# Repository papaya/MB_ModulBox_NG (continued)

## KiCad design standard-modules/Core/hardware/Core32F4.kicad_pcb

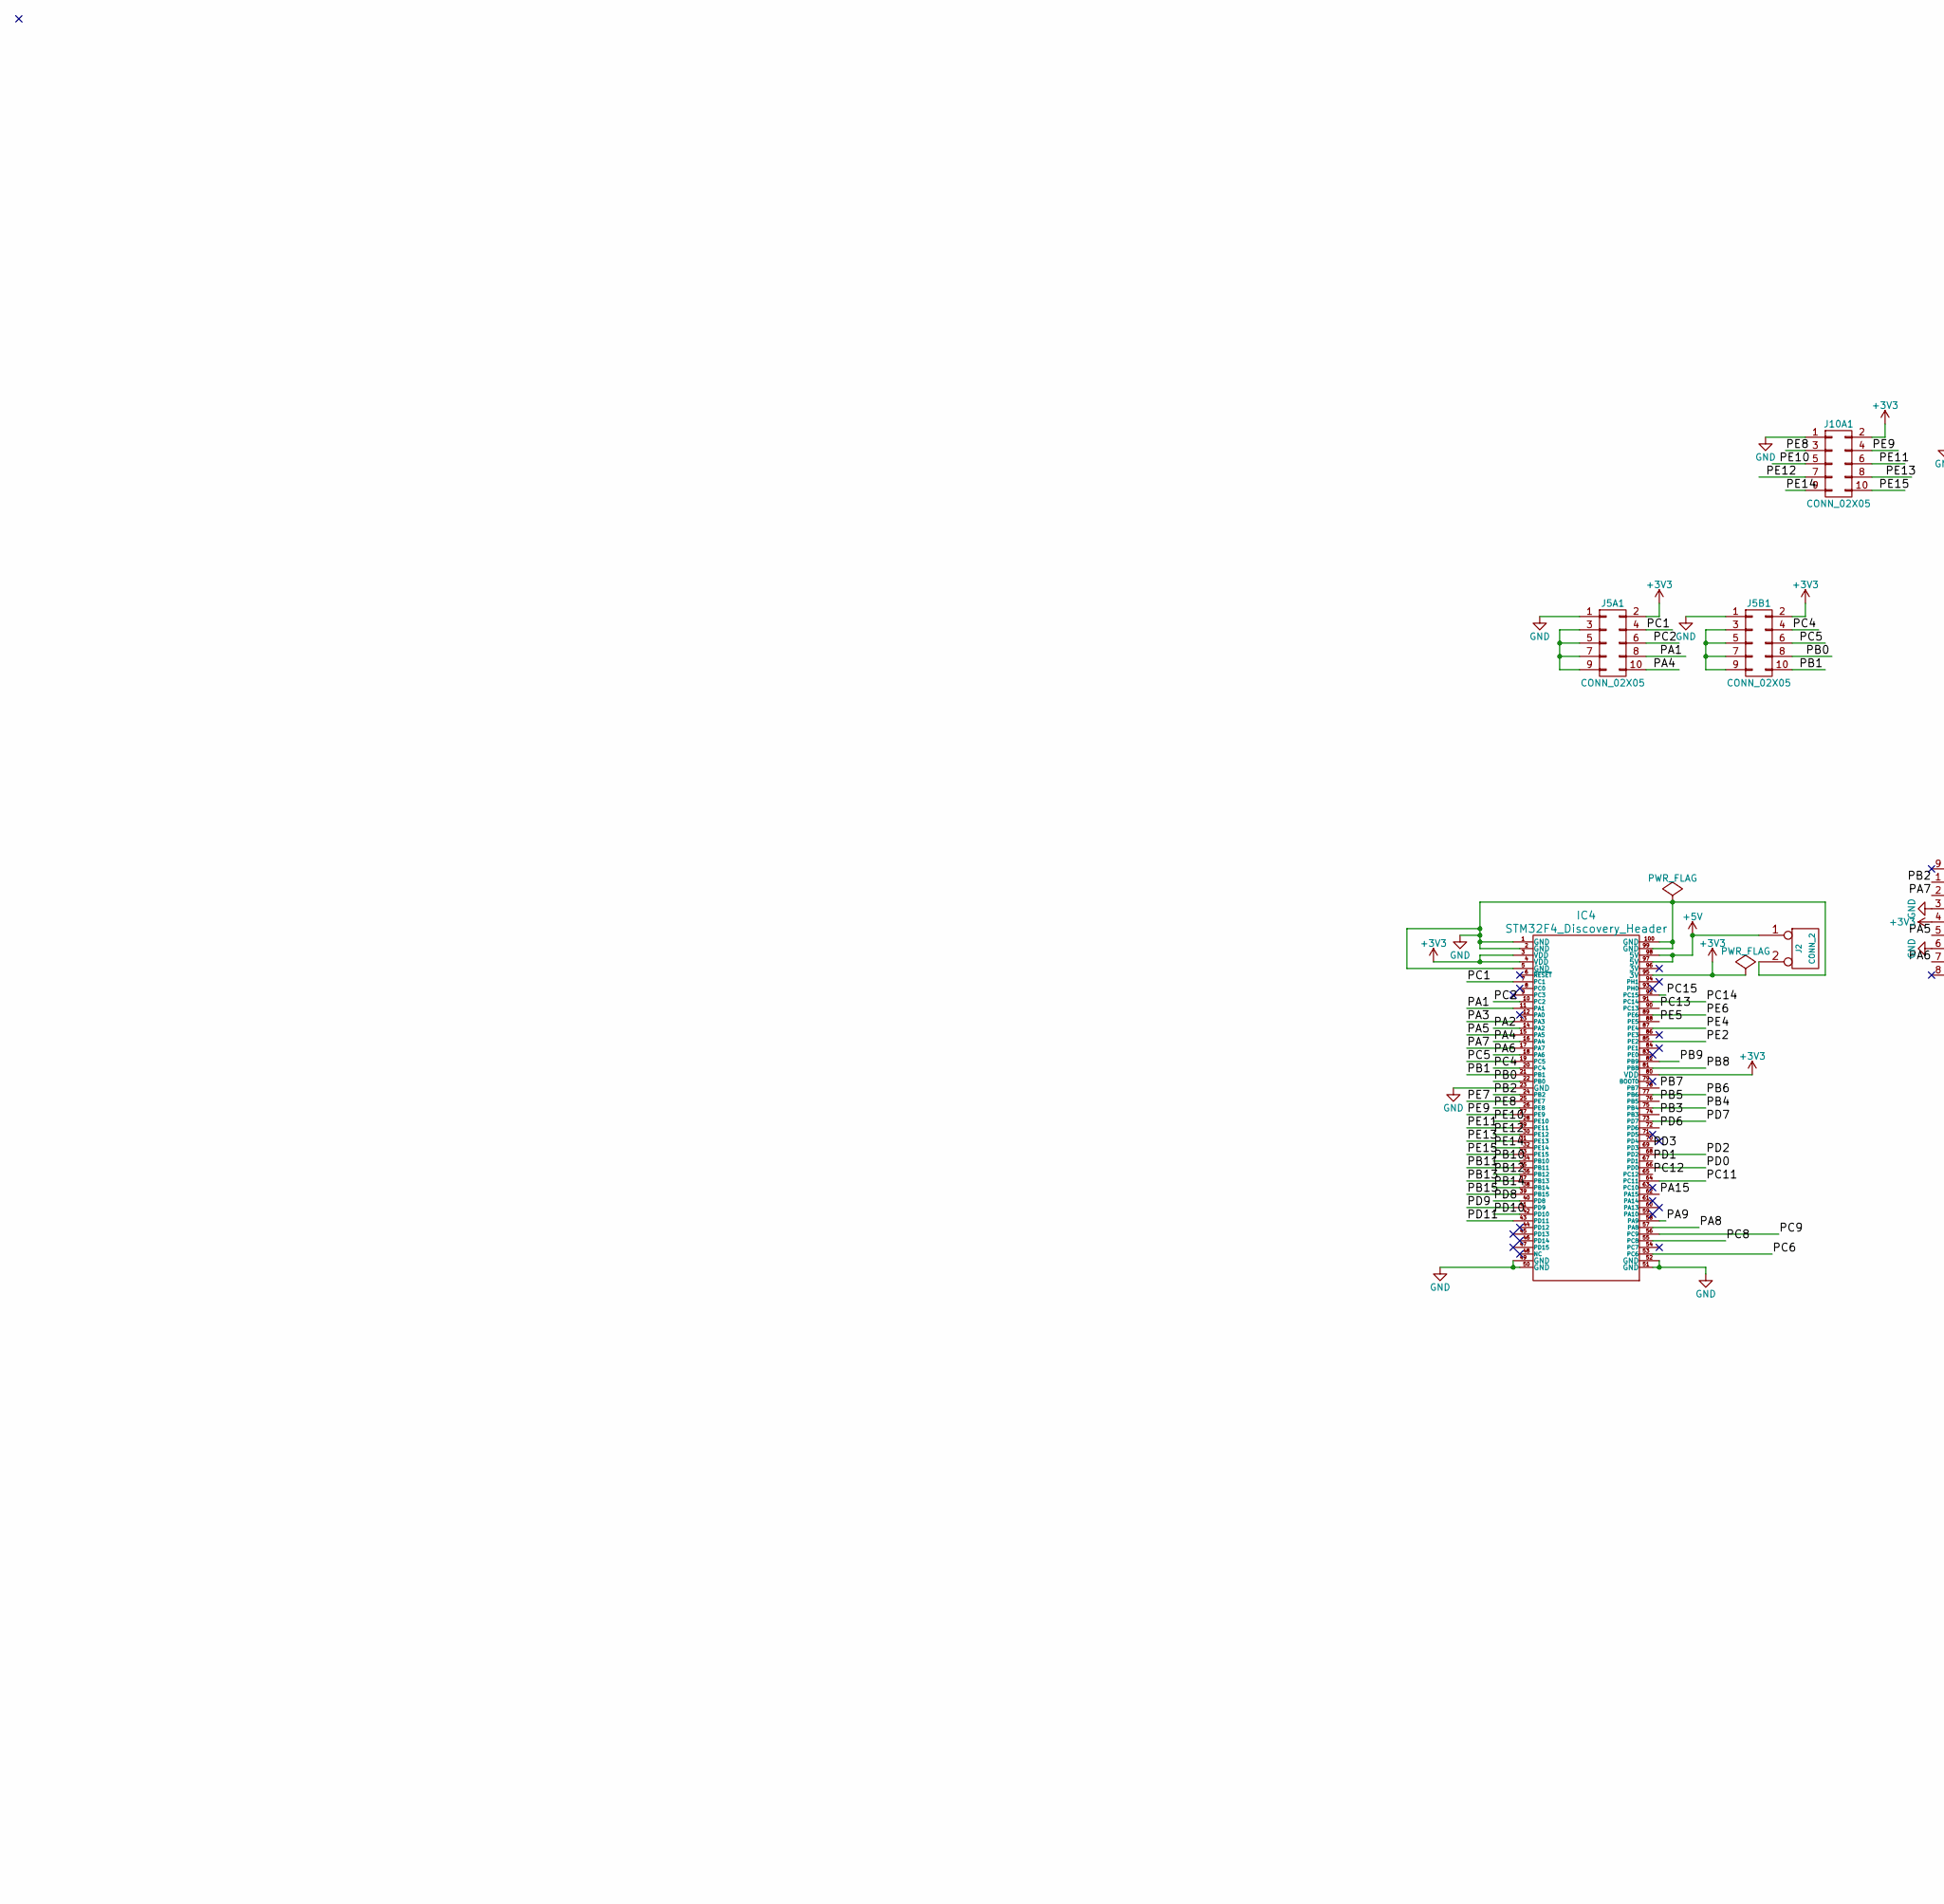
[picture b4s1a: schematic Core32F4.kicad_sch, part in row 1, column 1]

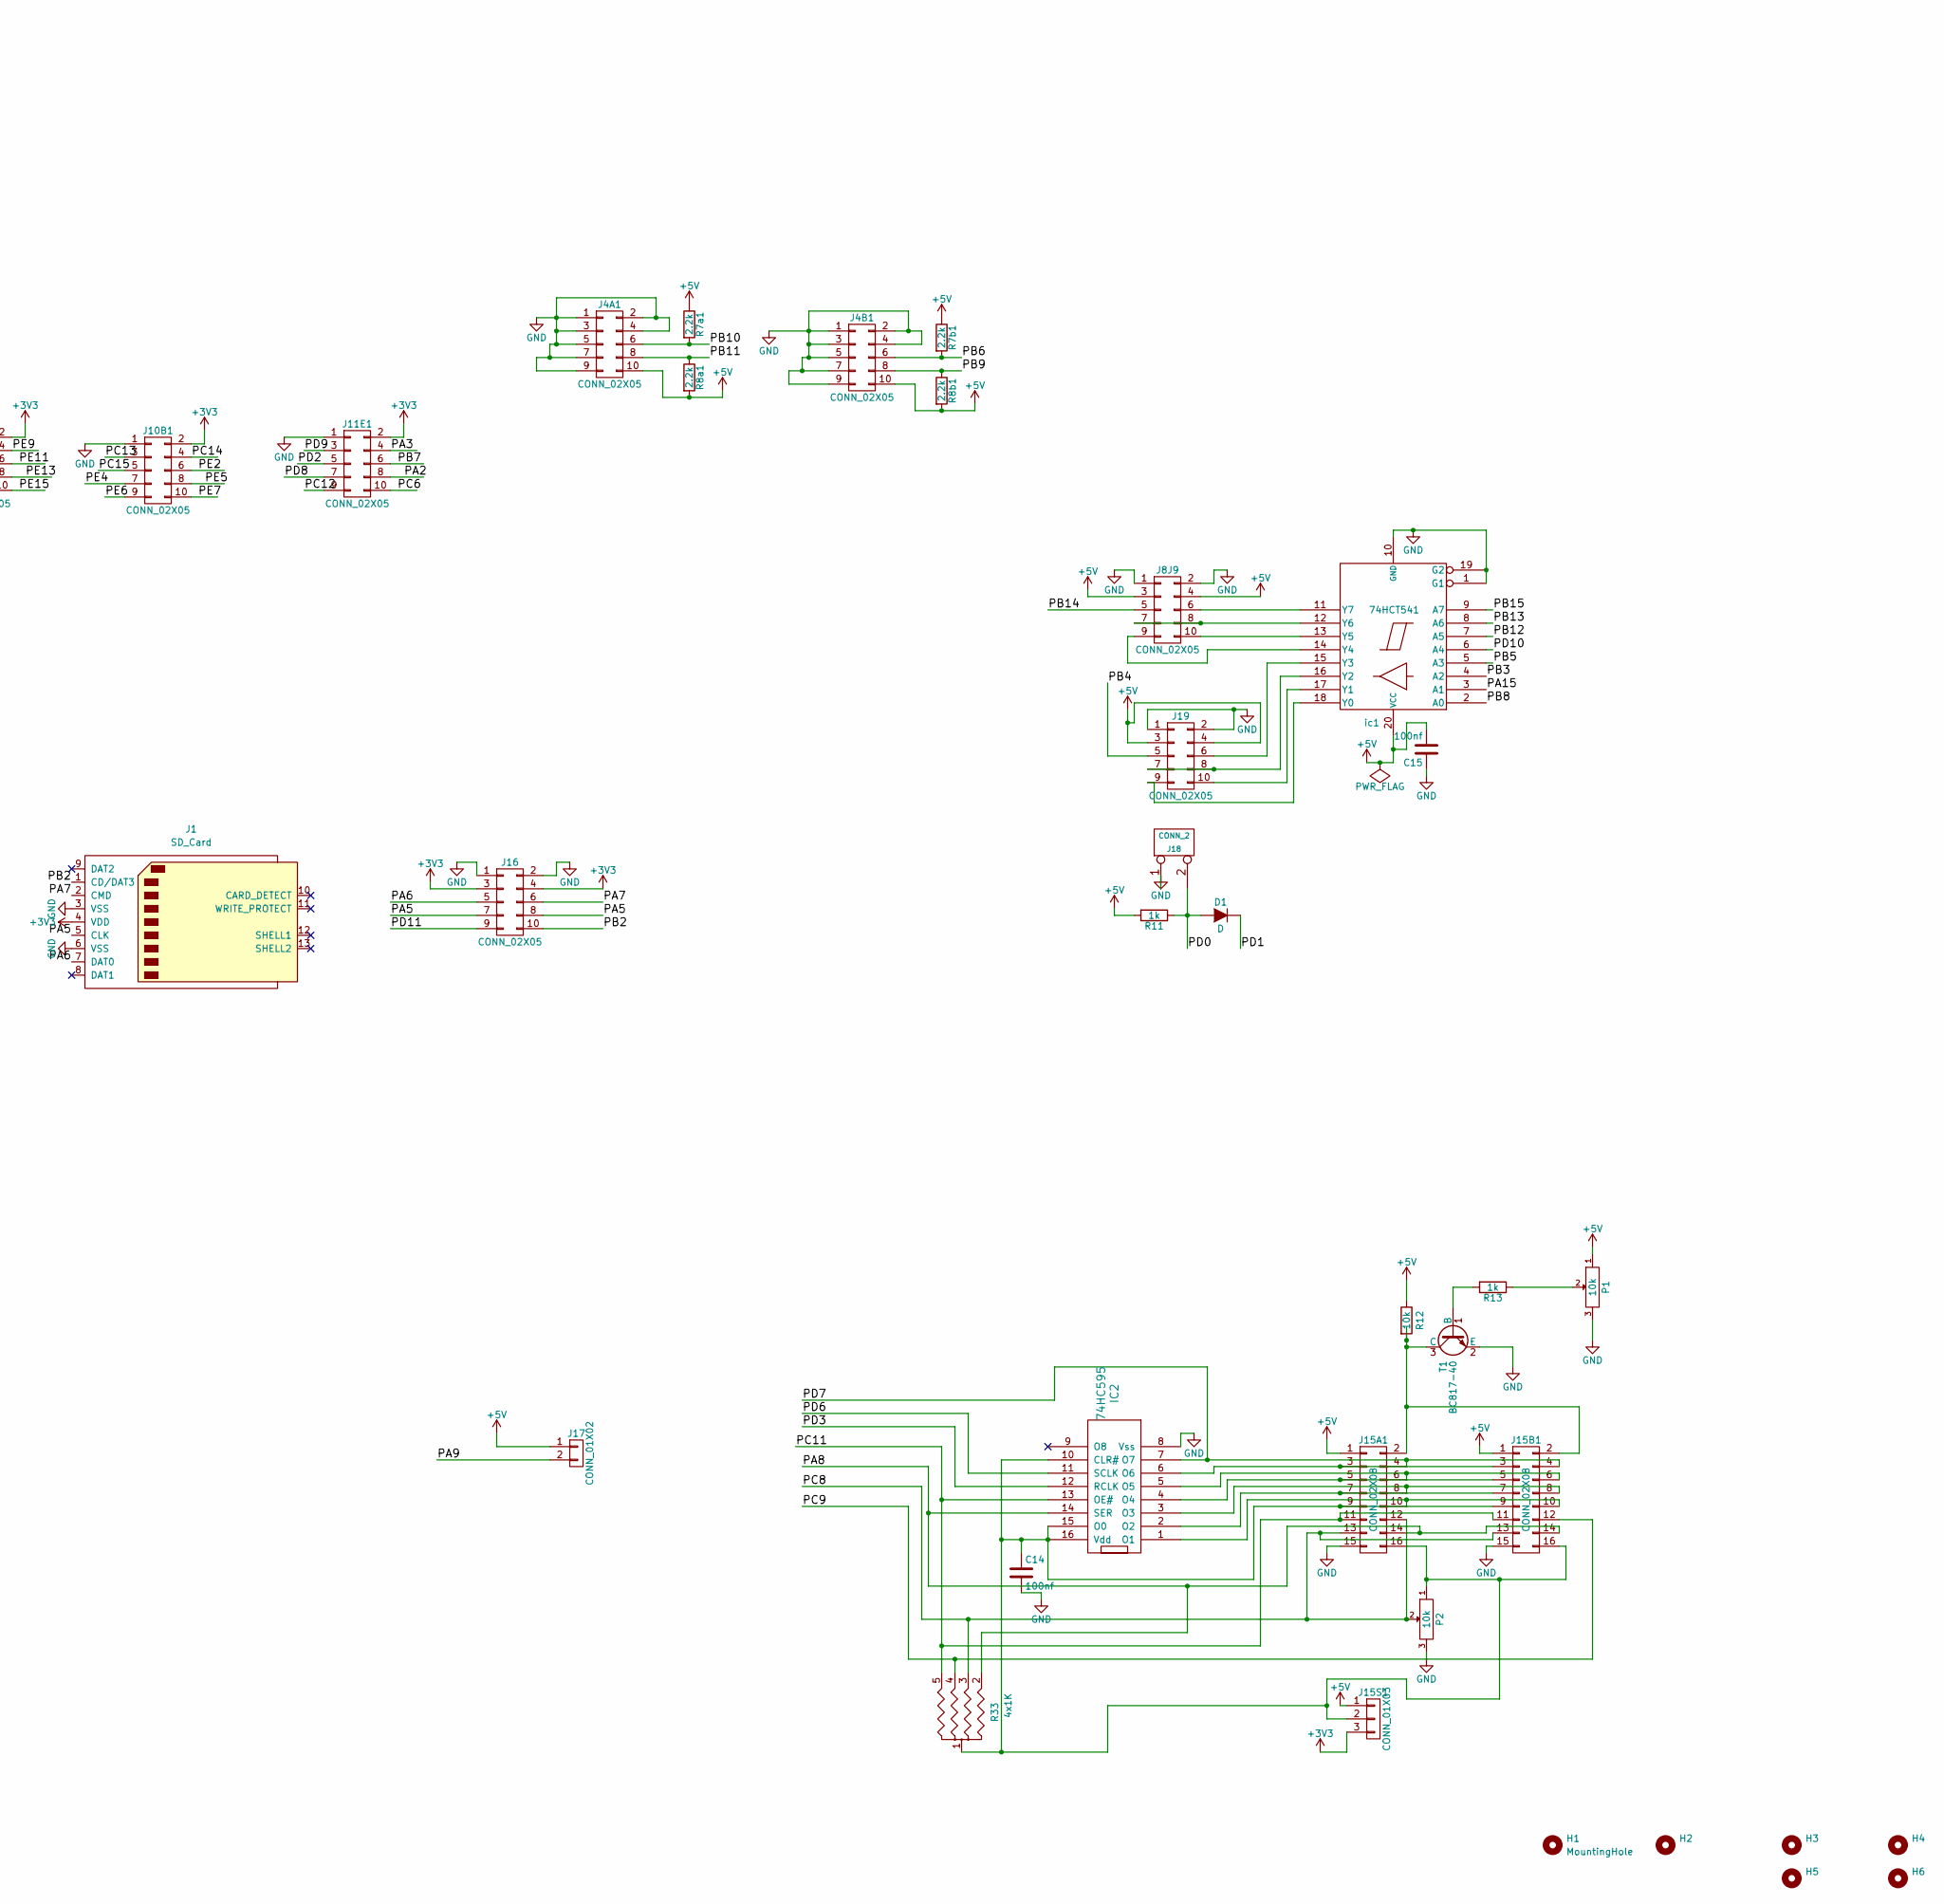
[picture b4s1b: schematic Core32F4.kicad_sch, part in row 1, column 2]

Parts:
C14, C15: 100nf; C_Disc_D3.8mm_W2.6mm_P2.50mm
D1: D; Diode_DO-35_SOD27_Horizontal_RM10
H1, H2, H3, H4, H5, H6: MountingHole; MountingHole_3.2mm_M3_ISO7380_Pad
IC2: 74HC595; DIP-16_W7.62mm_LongPads
IC4: STM32F4_Discovery_Header; stm32f4_discovery_header_ksir
J1: SD_Card; SDRSMT2MQ
J2, J18: CONN_2; PinHeader_1x02_P2.54mm_Vertical
J4A1, J4B1, J5A1, J5B1, J8J9, J10A1, J10B1, J11E1, J16, J19: CONN_02X05; IDC-Header_2x05_P2.54mm_Vertical
J15A1, J15B1: CONN_02X08; IDC-Header_2x08_P2.54mm_Vertical
J15S1: CONN_01X03; PinHeader_1x03_P2.54mm_Vertical
J17: CONN_01X02; PinHeader_1x02_P2.54mm_Vertical
P1, P2: 10k; Potentiometer_VishaySpectrol-Econtrim-Type36T
R7a1, R7b1, R8a1, R8b1: 2.2k; R_Axial_DIN0204_L3.6mm_D1.6mm_P7.62mm_Horizontal
R11, R13: 1k; R_Axial_DIN0204_L3.6mm_D1.6mm_P7.62mm_Horizontal
R12: 10k; R_Axial_DIN0204_L3.6mm_D1.6mm_P7.62mm_Horizontal
R33: 4x1K; R_Array_SIP5
T1: BC817-40; bc337
ic1: 74HCT541; DIP-20_W7.62mm_LongPads

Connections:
+3V3: IC4.3 (VDD), IC4.4 (VDD), IC4.80 (VDD), IC4.95 (3V), J1.4 (VDD), J5A1.2, J5B1.2, J10A1.2, J10B1.2, J11E1.2, J15S1.3, J16.3, J16.4
+5V: C15.2, IC4.97 (5V), IC4.98 (5V), J2.1, J4A1.10, J4B1.10, J8J9.3, J8J9.4, J15A1.1, J15B1.1, J15S1.1, J17.1, J19.3, J19.4, P1.1, R7a1.1, R7b1.1, R8a1.2, R8b1.2, R11.2, R12.1, ic1.20 (VCC)
/PA1: IC4.11 (PA1), J5A1.8
/PA2: IC4.14 (PA2), J11E1.8
/PA3: IC4.13 (PA3), J11E1.4
/PA4: IC4.16 (PA4), J5A1.10
/PA5: IC4.15 (PA5), J1.5 (CLK), J16.7, J16.8
/PA6: IC4.18 (PA6), J1.7 (DAT0), J16.5
/PA7: IC4.17 (PA7), J1.2 (CMD), J16.6
/PA8: IC2.14 (SER), IC4.57 (PA8), J15A1.14, J15B1.14, R33.2
/PA9: IC4.58 (PA9), J17.2
/PA15: IC4.62 (PA15), ic1.3 (A1)
/PB0: IC4.22 (PB0), J5B1.8
/PB1: IC4.21 (PB1), J5B1.10
/PB2: IC4.24 (PB2), J1.1 (CD/DAT3), J16.10
/PB3: IC4.74 (PB3), ic1.4 (A2)
/PB4: IC4.75 (PB4), J19.5
/PB5: IC4.76 (PB5), ic1.5 (A3)
/PB6: IC4.77 (PB6), J4B1.6, R7b1.2
/PB7: IC4.78 (PB7), J11E1.6
/PB8: IC4.81 (PB8), ic1.2 (A0)
/PB9: IC4.82 (PB9), J4B1.8, R8b1.1
/PB10: IC4.34 (PB10), J4A1.6, R7a1.2
/PB11: IC4.35 (PB11), J4A1.8, R8a1.1
/PB12: IC4.36 (PB12), ic1.7 (A5)
/PB13: IC4.37 (PB13), ic1.8 (A6)
/PB14: IC4.38 (PB14), J8J9.5
/PB15: IC4.39 (PB15), ic1.9 (A7)
/PC1: IC4.7 (PC1), J5A1.4
/PC2: IC4.10 (PC2), J5A1.6
/PC4: IC4.20 (PC4), J5B1.4
/PC5: IC4.19 (PC5), J5B1.6
/PC6: IC4.53 (PC6), J11E1.10
/PC8: IC4.55 (PC8), J15A1.12, J15A1.13, J15B1.13, P2.2, R33.3
/PC11: IC2.13 (OE#), IC4.64 (PC11), J15A1.11, J15B1.11, R33.5
/PC12: IC4.65 (PC12), J11E1.9
/PC13: IC4.90 (PC13), J10B1.3
/PC14: IC4.91 (PC14), J10B1.4
/PC15: IC4.92 (PC15), J10B1.5
/PD0: D1.2 (A), IC4.66 (PD0), J18.2 (PM), R11.1
/PD1: D1.1 (K), IC4.67 (PD1)
/PD2: IC4.68 (PD2), J11E1.5
/PD3: IC2.12 (RCLK), IC4.69 (PD3)
/PD6: IC2.11 (SCLK), IC4.72 (PD6)
/PD7: IC2.7 (O7), IC4.73 (PD7), J15A1.4, J15B1.4
/PD8: IC4.40 (PD8), J11E1.7
/PD9: IC4.41 (PD9), J11E1.3
/PD10: IC4.42 (PD10), ic1.6 (A4)
/PD11: IC4.43 (PD11), J16.9
/PE2: IC4.85 (PE2), J10B1.6
/PE4: IC4.87 (PE4), J10B1.7
/PE5: IC4.88 (PE5), J10B1.8
/PE6: IC4.89 (PE6), J10B1.9
/PE7: IC4.25 (PE7), J10B1.10
/PE8: IC4.26 (PE8), J10A1.3
/PE9: IC4.27 (PE9), J10A1.4
/PE10: IC4.28 (PE10), J10A1.5
/PE11: IC4.29 (PE11), J10A1.6
/PE12: IC4.30 (PE12), J10A1.7
/PE13: IC4.31 (PE13), J10A1.8
/PE14: IC4.32 (PE14), J10A1.9
/PE15: IC4.33 (PE15), J10A1.10
unnamed: C14.1, IC2.10 (CLR#), IC2.15 (O0), IC2.16 (Vdd), J15A1.9, J15A1.16, J15B1.9, J15B1.16, J15S1.2, P2.1, R33.1
unnamed: IC2.1 (O1), J15A1.10, J15B1.10
unnamed: IC2.2 (O2), J15A1.7, J15B1.7
unnamed: IC2.3 (O3), J15A1.8, J15B1.8
unnamed: IC2.4 (O4), J15A1.5, J15B1.5
unnamed: IC2.5 (O5), J15A1.6, J15B1.6
unnamed: IC2.6 (O6), J15A1.3, J15B1.3
unnamed: J5A1.3, J5A1.5, J5A1.7, J5A1.9
unnamed: J5B1.3, J5B1.5, J5B1.7, J5B1.9
unnamed: J8J9.6, ic1.11 (Y7)
unnamed: J8J9.7, J8J9.8, ic1.12 (Y6)
unnamed: J8J9.9, ic1.14 (Y4)
unnamed: J8J9.10, ic1.13 (Y5)
unnamed: J15A1.2, J15B1.2, R12.2, T1.3 (C)
unnamed: J19.6, ic1.15 (Y3)
unnamed: J19.7, J19.8, ic1.16 (Y2)
unnamed: J19.9, ic1.18 (Y0)
unnamed: J19.10, ic1.17 (Y1)
unnamed: P1.2, R13.1
unnamed: R13.2, T1.1 (B)

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
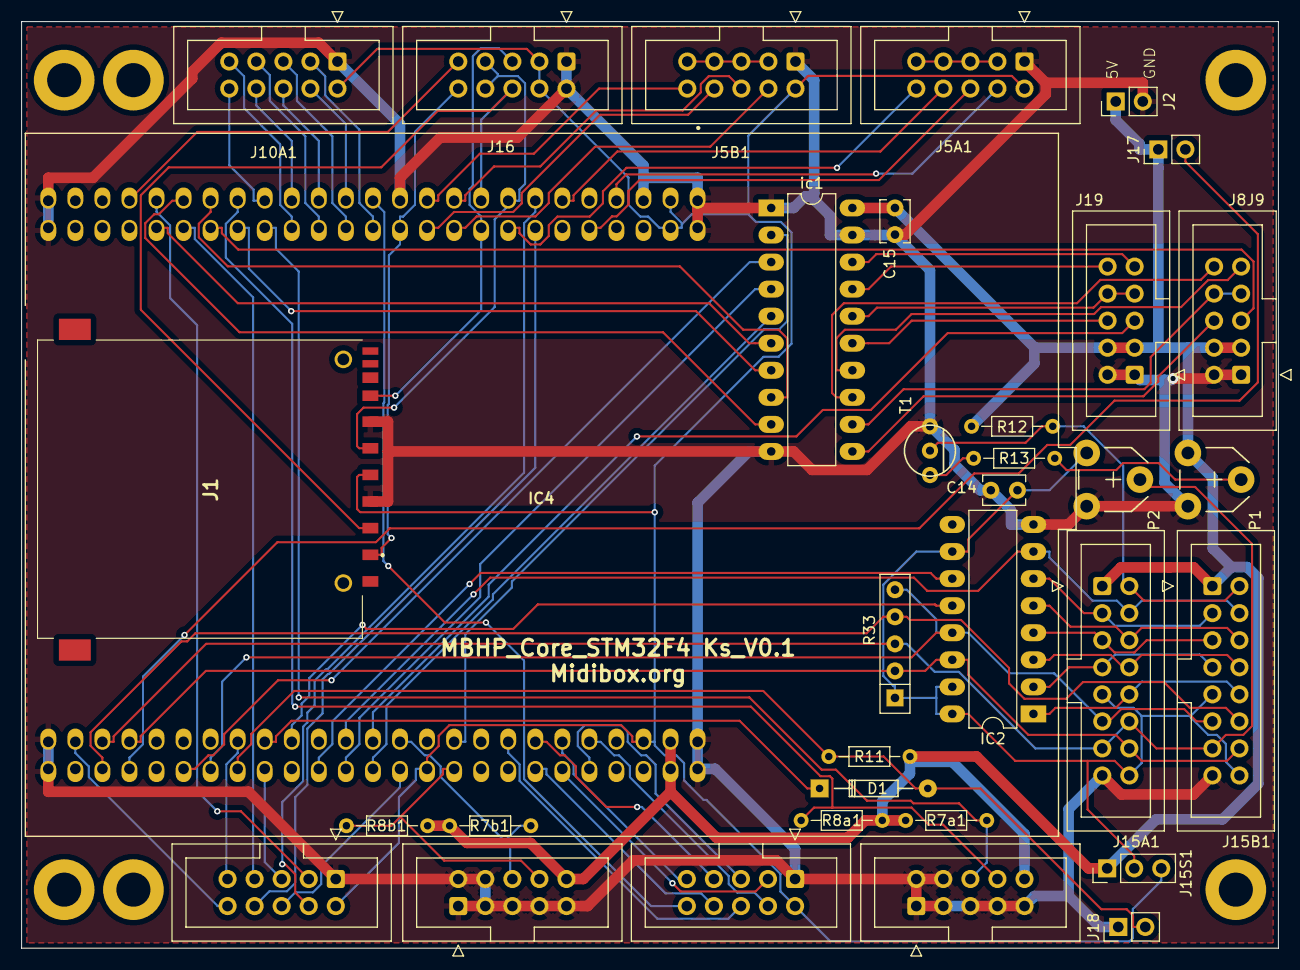
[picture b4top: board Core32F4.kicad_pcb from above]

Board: 2 copper layers, 118.0 x 87.0 mm, 40 parts (0 on the bottom side), 84 nets.

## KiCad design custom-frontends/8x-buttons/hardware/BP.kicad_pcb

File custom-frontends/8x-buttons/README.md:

# 8x-buttons — Module custom 8 boutons poussoirs (DIN + DOUT)

## Description

Module boutons poussoirs (8 canaux) pour l'envoi d'événements MIDI numériques (Note On/Off, CC, etc.). La carte se branche sur le **bus DIN** (entrées digitales) du contrôleur MIDIbox NG et fournit en plus **8 sorties DOUT** pour piloter des LEDs.

## Spécifications techniques

- 8 boutons poussoirs mécaniques **à LED incorporée** (empreinte `switch_led_mec`)
- 8 LED supplémentaires (empreinte `LED Switch mec`), câblées en sortie
- **2 connecteurs IDC 2x05 P2.54mm** : `J1` = 8 entrées DIN, `J2` = 8 sorties DOUT
- **Aucune résistance de pull-up sur la carte** : le pull-up 10 kΩ est porté par le module **DIN** (74HC165), conformément à la référence MIDIbox
- Aucun registre à décalage sur la carte : les entrées et sorties sont balayées par les registres du module DIN / DOUT

## Composants principaux

| Type | Dénomination | Qté |
|------|-------------|-----|
| Bouton poussoir mécanique à LED | `switch_led_mec` | 8 |
| LED | `LED Switch mec` | 8 |
| Connecteur | IDC Header 2x05 P2.54mm Vertical (`J1`, `J2`) | 2 |
| Vis de fixation | MountingHole 3.2mm M3 | 4 |

> Les versions antérieures de cette page mentionnaient un **connecteur D-Sub 24 broches** et **8 pull-ups 10 kΩ** sur la carte : **ces deux éléments sont absents du schéma KiCad**. Le raccordement se fait par IDC 2x05.

## Brochage / Mapping MIDIbox NG

### `J1` — 8 entrées DIN (vers le module DIN 74HC165, chainage `J8`/`J9` du Core)

| Broche | Signal | Description |
|--------|--------|-------------|
| 1 | GND | Masse commune (contact du bouton) |
| 2 | — | Non connectée |
| 3 | `J1-D7` | Bouton **SW8** |
| 4 | `J1-D6` | Bouton **SW7** |
| 5 | `J1-D5` | Bouton **SW6** |
| 6 | `J1-D4` | Bouton **SW5** |
| 7 | `J1-D3` | Bouton **SW4** |
| 8 | `J1-D2` | Bouton **SW3** |
| 9 | `J1-D1` | Bouton **SW2** |
| 10 | `J1-D0` | Bouton **SW1** |

> Chaque bouton est un contact **entre sa broche `J1-Dx` et GND** (broche 1). Le niveau haut est assuré par le pull-up 10 kΩ du module DIN.

### `J2` — 8 sorties DOUT (vers le module DOUT 74HC595, chainage `J8`/`J9` du Core)

| Broche | Signal | Description |
|--------|--------|-------------|
| 1 | GND | Masse commune (cathode des LED) |
| 2 | — | Non connectée |
| 3 | `D8-A` | LED **D8** (anode) |
| 4 | `D7-A` | LED **D7** (anode) |
| 5 | `D6-A` | LED **D6** (anode) |
| 6 | `D5-A` | LED **D5** (anode) |
| 7 | `D4-A` | LED **D4** (anode) |
| 8 | `D3-A` | LED **D3** (anode) |
| 9 | `D2-A` | LED **D2** (anode) |
| 10 | `D1-A` | LED **D1** (anode) |

> L'anode de chaque LED est tirée vers la sortie DOUT correspondante ; la cathode est sur GND. La résistance de limitation (**220 Ω**) est portée par le module **DOUT** (74HC595), pas par cette carte.

## Notes de montage et astuces DIY

- Vérifier la configuration des entrées (active haut / active bas) avant câblage
- Pour un fonctionnement « high-active », il faut inverser le câblage du pull-up côté module DIN (procédure décrite sur [ucapps.de/mbhp_din](https://www.ucapps.de/mbhp_din.html))
- La LED de chaque bouton est câblée indépendamment sur `J2` : une LED du bouton peut être allumée indépendamment de l'état du bouton

## Documentation de fabrication

- `hardware/` : sources KiCad (`BP.*`)
- `hardware/3D/` : modèle 3D du boîtier (`BP V3.wrl`)
- `production/` : Gerbers, BOM (`bom.csv`), netlist, archives de fabrication
## Assets de visualisation

| Type | Fichier | Description |
|------|---------|-------------|
| Top view | `3d-top.png` | Vue de dessus du PCB |
| Screenshot 1 | `Screenshot%202023-05-19%20163416.png` | Capture d'écran du design |
| Screenshot 2 | `Screenshot%202023-05-19%20202624.png` | Capture d'écran du design |
---

## Conception & Compatibilité

Carte d'interface **originale MB MODULBOX NG** (conception Ksir), compatible avec les bus et modules du système MIDIbox NG. Ce n'est **pas** un module officiel MIDIbox.

> **Origine et usage :** conception originale MB MODULBOX NG, prévue pour le DIY/personnel. Aucune licence formelle n'est publiée dans le dépôt ; voir le README racine. **Aucune garantie ni engagement** n'est fourni sur la justesse du câblage ou du routage.

> ⚠️ **Avertissement :** documentation de passion, **non professionnelle**. Fournie **sans garantie ni engagement**, **sans support technique**. Des **erreurs sont possibles** (schémas, valeurs, câblage). À vos risques et périls : vérifiez tout avant de fabriquer et de mettre sous tension.

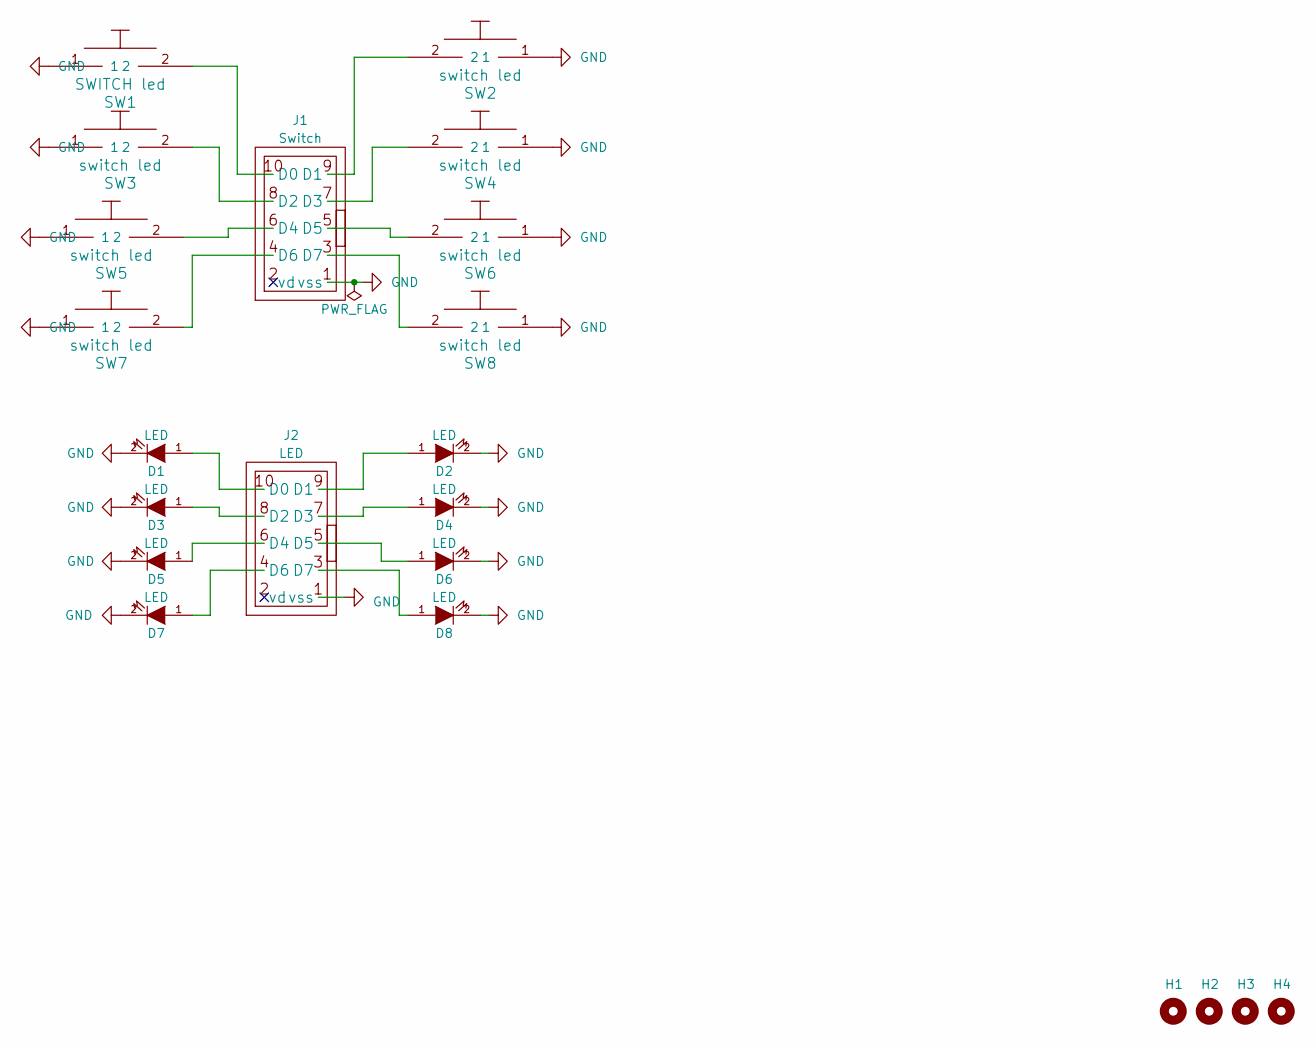
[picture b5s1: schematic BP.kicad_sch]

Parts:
D1, D2, D3, D4, D5, D6, D7, D8: LED; LED Switch mec
H1, H2, H3, H4: MountingHole; MountingHole_3.2mm_M3
J1, J2: IDC-Header_2x05_P2.54mm_Vertical
SW1: SWITCH led; switch_led_mec
SW2, SW3, SW4, SW5, SW6, SW7, SW8: switch led; switch_led_mec

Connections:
GND: D1.2 (K), D2.2 (K), D3.2 (K), D4.2 (K), D5.2 (K), D6.2 (K), D7.2 (K), D8.2 (K), J1.1 (vss), J2.1 (vss), SW1.1, SW2.1, SW3.1, SW4.1, SW5.1, SW6.1, SW7.1, SW8.1
unnamed: D1.1 (A), J2.10 (D0)
unnamed: D2.1 (A), J2.9 (D1)
unnamed: D3.1 (A), J2.8 (D2)
unnamed: D4.1 (A), J2.7 (D3)
unnamed: D5.1 (A), J2.6 (D4)
unnamed: D6.1 (A), J2.5 (D5)
unnamed: D7.1 (A), J2.4 (D6)
unnamed: D8.1 (A), J2.3 (D7)
unnamed: J1.10 (D0), SW1.2
unnamed: J1.9 (D1), SW2.2
unnamed: J1.8 (D2), SW3.2
unnamed: J1.7 (D3), SW4.2
unnamed: J1.6 (D4), SW5.2
unnamed: J1.5 (D5), SW6.2
unnamed: J1.4 (D6), SW7.2
unnamed: J1.3 (D7), SW8.2

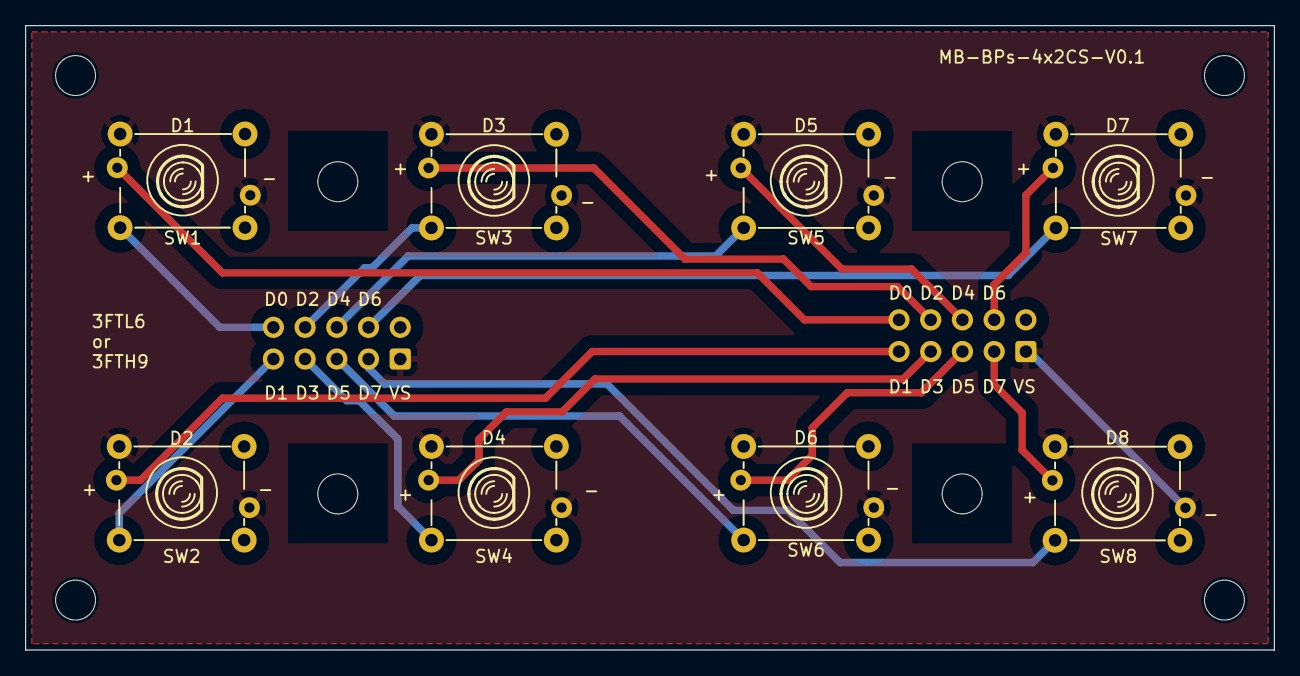
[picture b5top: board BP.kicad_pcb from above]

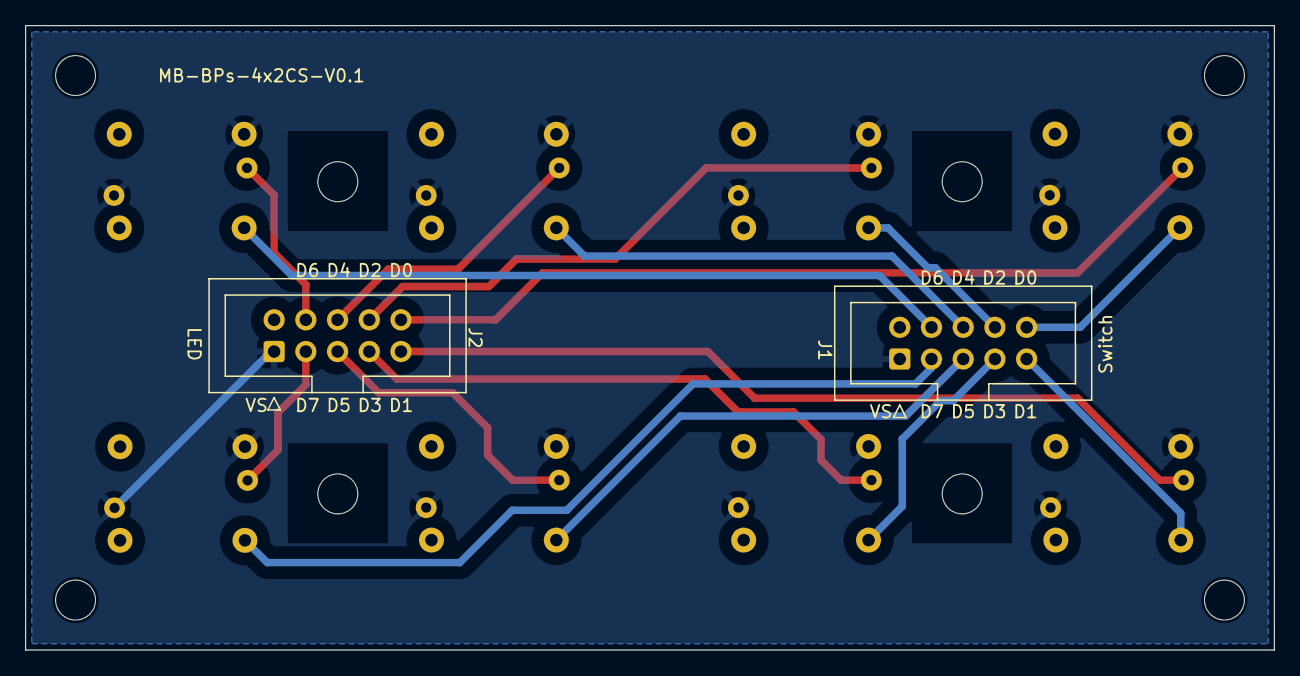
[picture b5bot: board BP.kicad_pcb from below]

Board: 2 copper layers, 100.0 x 50.0 mm, 26 parts (2 on the bottom side), 17 nets.

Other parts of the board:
H1#2, H2#2, H3#2, H4#2: MountingHole; MountingHole_3.2mm_M3

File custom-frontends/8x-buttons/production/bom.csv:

Designator,Footprint,Quantity,Value,LCSC Part #
"D1, D2, D3, D4, D5, D6, D7, D8",LED Switch mec,8,LED,
ENC1,EC12E24204A8,1,MENU,
"H1_3, H1_2, H1, H2_3, H2_2, H2, H3_3, H3_2, H3, H4_3, H4_2, H4",MountingHole_3.2mm_M3,12,MountingHole,
"J1, J2_2, J2",IDC-Header_2x05_P2.54mm_Vertical,3,IDC-Header_2x05_P2.54mm_Vertical,
"SW1, SW2, SW3, SW4, SW5, SW6, SW7, SW8",switch_led_mec,8,SWITCH led,
SWc1,124110828,1,shift,
SWc2,124110828,1,soft4,
SWc3,124110828,1,soft 3,
SWc4,124110828,1,soft 2,
SWc5,124110828,1,soft 1,
SWc6,124110828,1,MENU,

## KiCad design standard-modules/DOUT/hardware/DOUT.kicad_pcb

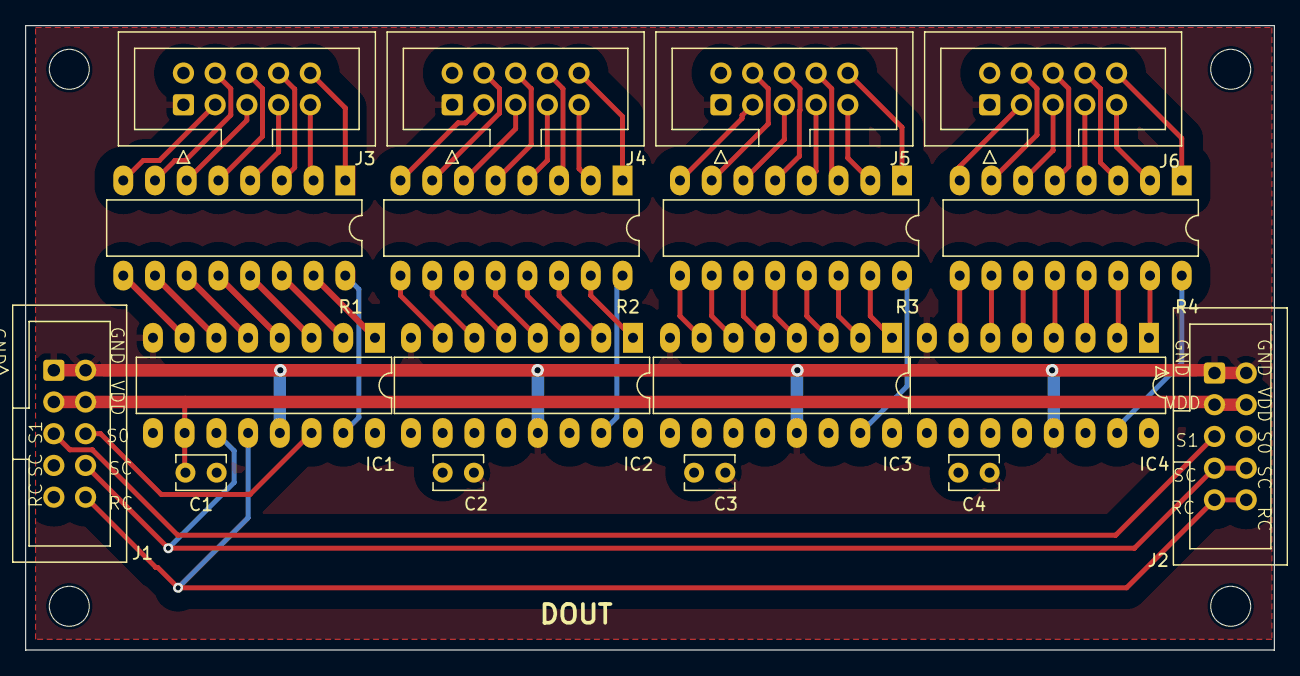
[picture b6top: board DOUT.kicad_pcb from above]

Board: 2 copper layers, 100.0 x 50.0 mm, 22 parts (0 on the bottom side), 74 nets.

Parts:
C1, C2, C3, C4: 100NF; C_Disc_D3.8mm_W2.6mm_P2.50mm
H1, H2, H3, H4: MountingHole; MountingHole_3.2mm_M3
IC1, IC2, IC3, IC4: SN74HC595N; DIP-16_74h595
J1, J2: sin_in; IDC-Header_2x05_P2.54mm_Vertical_ksr_TO_J8_J9
J3, J4, J5, J6: sin_in; IDC-Header_2x05_P2.54mm_Vertical
R1: 220 ohm; DIP-16_R220_network
R2, R3, R4: 220 ohm; DIP-16_W7.62mm_LongPads

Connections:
+5V: C1.2, C2.2, C3.2, C4.2, IC1.10 (~SRCLR), IC1.16 (VCC), IC2.10 (~SRCLR), IC2.16 (VCC), IC3.10 (~SRCLR), IC3.16 (VCC), IC4.10 (~SRCLR), IC4.16 (VCC), J1.3, J1.4, J2.3, J2.4
/DOUT_RC: IC1.12 (RCLK), IC2.12 (RCLK), IC3.12 (RCLK), IC4.12 (RCLK), J1.10, J2.9, J2.10
/DOUT_SC: IC1.11 (SRCLK), IC2.11 (SRCLK), IC3.11 (SRCLK), IC4.11 (SRCLK), J1.8, J2.7, J2.8
/S0: IC1.14 (SER), J1.6
GND: C1.1, C2.1, C3.1, C4.1, IC1.8 (GND), IC1.13 (~OE), IC2.8 (GND), IC2.13 (~OE), IC3.8 (GND), IC3.13 (~OE), IC4.8 (GND), IC4.13 (~OE), J1.1, J1.2, J2.1, J2.2, J3.1, J4.1, J5.1, J6.1
unnamed: IC1.15 (QA), R1.16 (R1.2)
unnamed: IC1.1 (QB), R1.15 (R2.2)
unnamed: IC1.2 (QC), R1.14 (R3.2)
unnamed: IC1.3 (QD), R1.13 (R4.2)
unnamed: IC1.4 (QE), R1.12 (R5.2)
unnamed: IC1.5 (QF), R1.11 (R6.2)
unnamed: IC1.6 (QG), R1.10 (R7.2)
unnamed: IC1.7 (QH_1), R1.9 (R8.2)
unnamed: IC1.9 (QH_2), IC2.14 (SER)
unnamed: IC2.15 (QA), R2.16 (R1.2)
unnamed: IC2.1 (QB), R2.15 (R2.2)
unnamed: IC2.2 (QC), R2.14 (R3.2)
unnamed: IC2.3 (QD), R2.13 (R4.2)
unnamed: IC2.4 (QE), R2.12 (R5.2)
unnamed: IC2.5 (QF), R2.11 (R6.2)
unnamed: IC2.6 (QG), R2.10 (R7.2)
unnamed: IC2.7 (QH_1), R2.9 (R8.2)
unnamed: IC2.9 (QH_2), IC3.14 (SER)
unnamed: IC3.15 (QA), R3.16 (R1.2)
unnamed: IC3.1 (QB), R3.15 (R2.2)
unnamed: IC3.2 (QC), R3.14 (R3.2)
unnamed: IC3.3 (QD), R3.13 (R4.2)
unnamed: IC3.4 (QE), R3.12 (R5.2)
unnamed: IC3.5 (QF), R3.11 (R6.2)
unnamed: IC3.6 (QG), R3.10 (R7.2)
unnamed: IC3.7 (QH_1), R3.9 (R8.2)
unnamed: IC3.9 (QH_2), IC4.14 (SER)
unnamed: IC4.15 (QA), R4.16 (R1.2)
unnamed: IC4.1 (QB), R4.15 (R2.2)
unnamed: IC4.2 (QC), R4.14 (R3.2)
unnamed: IC4.3 (QD), R4.13 (R4.2)
unnamed: IC4.4 (QE), R4.12 (R5.2)
unnamed: IC4.5 (QF), R4.11 (R6.2)
unnamed: IC4.6 (QG), R4.10 (R7.2)
unnamed: IC4.7 (QH_1), R4.9 (R8.2)
unnamed: IC4.9 (QH_2), J2.6
unnamed: J1.5, J2.5
unnamed: J3.10, R1.1 (R1.1)
unnamed: J3.9, R1.2 (R2.1)
unnamed: J3.8, R1.3 (R3.1)
unnamed: J3.7, R1.4 (R4.1)
unnamed: J3.6, R1.5 (R5.1)
unnamed: J3.5, R1.6 (R6.1)
unnamed: J3.4, R1.7 (R7.1)
unnamed: J3.3, R1.8 (R8.1)
unnamed: J4.10, R2.1 (R1.1)
unnamed: J4.9, R2.2 (R2.1)
unnamed: J4.8, R2.3 (R3.1)
unnamed: J4.7, R2.4 (R4.1)
unnamed: J4.6, R2.5 (R5.1)
unnamed: J4.5, R2.6 (R6.1)
unnamed: J4.4, R2.7 (R7.1)
unnamed: J4.3, R2.8 (R8.1)
unnamed: J5.10, R3.1 (R1.1)
unnamed: J5.9, R3.2 (R2.1)
unnamed: J5.8, R3.3 (R3.1)
unnamed: J5.7, R3.4 (R4.1)
unnamed: J5.6, R3.5 (R5.1)
unnamed: J5.5, R3.6 (R6.1)
unnamed: J5.4, R3.7 (R7.1)
unnamed: J5.3, R3.8 (R8.1)
unnamed: J6.10, R4.1 (R1.1)
unnamed: J6.9, R4.2 (R2.1)
unnamed: J6.8, R4.3 (R3.1)
unnamed: J6.7, R4.4 (R4.1)
unnamed: J6.6, R4.5 (R5.1)
unnamed: J6.5, R4.6 (R6.1)
unnamed: J6.4, R4.7 (R7.1)
unnamed: J6.3, R4.8 (R8.1)
